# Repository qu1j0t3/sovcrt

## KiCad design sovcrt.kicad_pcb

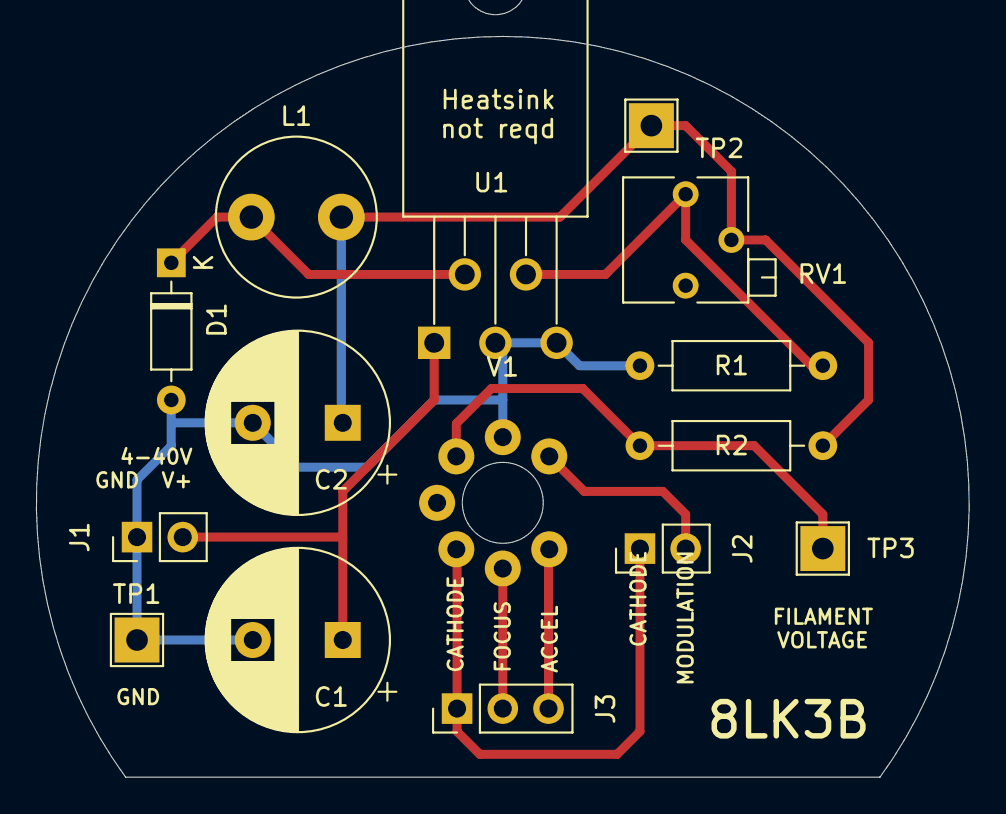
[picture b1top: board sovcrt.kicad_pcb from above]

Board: 2 copper layers, 51.8 x 41.2 mm, 15 parts (0 on the bottom side), 10 nets.

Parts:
C1: 220u 50V; CP_Radial_D10.0mm_P5.00mm
C2: 1000u 10V; CP_Radial_D10.0mm_P5.00mm
D1: SD103A; D_DO-35_SOD27_P7.62mm_Horizontal
J1, J2: Conn_01x02_Male; PinHeader_1x02_P2.54mm_Vertical
J3: Conn_01x03_Male; PinHeader_1x03_P2.54mm_Vertical
L1: 220u; L_Radial_D8.7mm_P5.00mm_Fastron_07HCP
R1: 4.7k; R_Axial_DIN0207_L6.3mm_D2.5mm_P10.16mm_Horizontal
R2: 3R3 1/2W; R_Axial_DIN0207_L6.3mm_D2.5mm_P10.16mm_Horizontal
RV1: 5k; Potentiometer_Bourns_3266P_Horizontal
TP1, TP2, TP3: TestPoint; TestPoint_THTPad_2.5x2.5mm_Drill1.2mm
U1: LM2575BT-ADJ; TO-220-5_P3.4x3.8mm_StaggerOdd_Lead7.13mm_TabDown
V1: 8LK3B; CRT_8LK3B_Samtec_sockets

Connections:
+12V: C1.1, J1.2, U1.1
GND: C1.2, C2.2, D1.2, J1.1, R1.1, TP1.1, U1.3, U1.5, V1.6
unnamed: C2.1, L1.2, R2.2, RV1.2, TP2.1
unnamed: D1.1, L1.1, U1.2
unnamed: J2.1, J3.1, V1.3
unnamed: J2.2, V1.7
unnamed: J3.2, V1.2
unnamed: J3.3, V1.1
unnamed: R1.2, RV1.3, U1.4
unnamed: R2.1, TP3.1, V1.5

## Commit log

2021-03-04 Initial commit.
2021-03-04 Tweaks.
2021-03-05 With @'RueNahcMohr's feedback hack.
2021-03-06 Increase size of output capacitor for proper smoothing; increase diode anode resistor.
2021-03-06 Fix capacitor values to fix stability.
2021-03-06 Remove diode hack in favour of a series resistor.

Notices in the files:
sovcrt.kicad_pcb:
Copyright (C) 2021
